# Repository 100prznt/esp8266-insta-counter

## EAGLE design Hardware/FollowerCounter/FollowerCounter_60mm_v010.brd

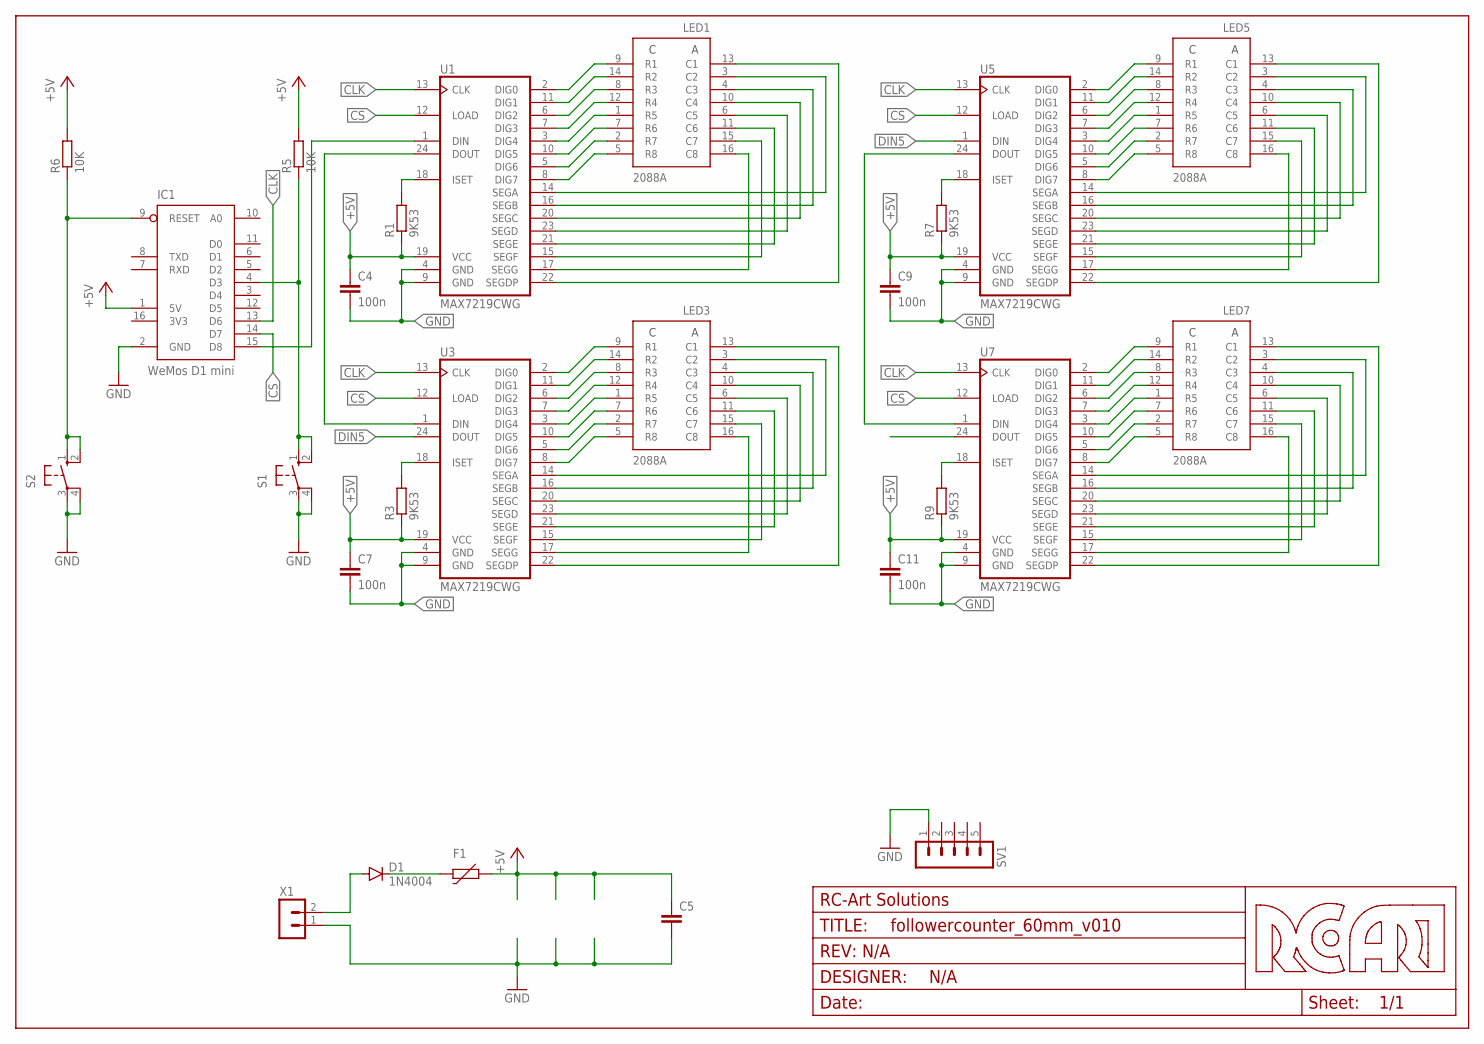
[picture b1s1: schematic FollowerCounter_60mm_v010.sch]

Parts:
C4, C7, C9, C11: 100n; C0805
C5: C-EUC0805; C0805
D1: 1N4004; DO41-10
F1: MF-MSMF075/24-EU; 1812
FRAME1: MF_FRAMEDEFAULT; MF_FRAME_DEFAULT
IC1: WeMos D1 mini; D1_MINI
LED1, LED3, LED5, LED7: 2088A; 8X8_60X60
R1, R3, R7, R9: 9K53; R0805
R5, R6: 10K; R0805
S1, S2: 10-XXS; B3FS-10XX
SV1: MA05-1
U1, U3, U5, U7: MAX7219CWG; SO24L
X1: MA02-1

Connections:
+5V: C4.1, C5.1, C7.1, C9.1, C11.1, F1.1, IC1.1 (5V), R1.1, R3.1, R5.2, R6.2, R7.1, R9.1, U1.19 (VCC), U3.19 (VCC), U5.19 (VCC), U7.19 (VCC)
CLK: IC1.13 (D6), U1.13 (CLK), U3.13 (CLK), U5.13 (CLK), U7.13 (CLK)
COL9: LED1.16 (C8), U1.17 (SEGG)
COL10: LED1.15 (C7), U1.15 (SEGF)
COL11: LED1.11 (C6), U1.21 (SEGE)
COL12: LED1.6 (C5), U1.23 (SEGD)
COL13: LED1.10 (C4), U1.20 (SEGC)
COL14: LED1.4 (C3), U1.16 (SEGB)
COL15: LED1.3 (C2), U1.14 (SEGA)
COL16: LED1.13 (C1), U1.22 (SEGDP)
COL25: LED3.16 (C8), U3.17 (SEGG)
COL26: LED3.15 (C7), U3.15 (SEGF)
COL27: LED3.11 (C6), U3.21 (SEGE)
COL28: LED3.6 (C5), U3.23 (SEGD)
COL29: LED3.10 (C4), U3.20 (SEGC)
COL30: LED3.4 (C3), U3.16 (SEGB)
COL31: LED3.3 (C2), U3.14 (SEGA)
COL32: LED3.13 (C1), U3.22 (SEGDP)
COL41: LED5.16 (C8), U5.17 (SEGG)
COL42: LED5.15 (C7), U5.15 (SEGF)
COL43: LED5.11 (C6), U5.21 (SEGE)
COL44: LED5.6 (C5), U5.23 (SEGD)
COL45: LED5.10 (C4), U5.20 (SEGC)
COL46: LED5.4 (C3), U5.16 (SEGB)
COL47: LED5.3 (C2), U5.14 (SEGA)
COL48: LED5.13 (C1), U5.22 (SEGDP)
COL57: LED7.16 (C8), U7.17 (SEGG)
COL58: LED7.15 (C7), U7.15 (SEGF)
COL59: LED7.11 (C6), U7.21 (SEGE)
COL60: LED7.6 (C5), U7.23 (SEGD)
COL61: LED7.10 (C4), U7.20 (SEGC)
COL62: LED7.4 (C3), U7.16 (SEGB)
COL63: LED7.3 (C2), U7.14 (SEGA)
COL64: LED7.13 (C1), U7.22 (SEGDP)
CS: IC1.14 (D7), U1.12 (LOAD), U3.12 (LOAD), U5.12 (LOAD), U7.12 (LOAD)
DIN1: IC1.15 (D8), U1.1 (DIN)
DIN5: U3.24 (DOUT), U5.1 (DIN)
DOUT1: U1.24 (DOUT), U3.1 (DIN)
DOUT5: U5.24 (DOUT), U7.1 (DIN)
DOUT7: U7.24 (DOUT)
GND: C4.2, C5.2, C7.2, C9.2, C11.2, IC1.2 (GND), S1.3, S1.4 (P1), S2.3, S2.4 (P1), SV1.1, U1.4 (GND), U1.9 (GND), U3.4 (GND), U3.9 (GND), U5.4 (GND), U5.9 (GND), U7.4 (GND), U7.9 (GND), X1.1
ISET1: R1.2, U1.18 (ISET)
ISET3: R3.2, U3.18 (ISET)
ISET5: R7.2, U5.18 (ISET)
ISET7: R9.2, U7.18 (ISET)
unnamed: IC1.4 (D3), R5.1, S1.1 (S), S1.2 (S1)
unnamed: IC1.9 (RESET), R6.1, S2.1 (S), S2.2 (S1)
unnamed: D1.A, X1.2
unnamed: D1.C, F1.2
ROW9: LED1.9 (R1), U1.2 (DIG0)
ROW10: LED1.14 (R2), U1.11 (DIG1)
ROW11: LED1.8 (R3), U1.6 (DIG2)
ROW12: LED1.12 (R4), U1.7 (DIG3)
ROW13: LED1.1 (R5), U1.3 (DIG4)
ROW14: LED1.7 (R6), U1.10 (DIG5)
ROW15: LED1.2 (R7), U1.5 (DIG6)
ROW16: LED1.5 (R8), U1.8 (DIG7)
ROW25: LED3.9 (R1), U3.2 (DIG0)
ROW26: LED3.14 (R2), U3.11 (DIG1)
ROW27: LED3.8 (R3), U3.6 (DIG2)
ROW28: LED3.12 (R4), U3.7 (DIG3)
ROW29: LED3.1 (R5), U3.3 (DIG4)
ROW30: LED3.7 (R6), U3.10 (DIG5)
ROW31: LED3.2 (R7), U3.5 (DIG6)
ROW32: LED3.5 (R8), U3.8 (DIG7)
ROW41: LED5.9 (R1), U5.2 (DIG0)
ROW42: LED5.14 (R2), U5.11 (DIG1)
ROW43: LED5.8 (R3), U5.6 (DIG2)
ROW44: LED5.12 (R4), U5.7 (DIG3)
ROW45: LED5.1 (R5), U5.3 (DIG4)
ROW46: LED5.7 (R6), U5.10 (DIG5)
ROW47: LED5.2 (R7), U5.5 (DIG6)
ROW48: LED5.5 (R8), U5.8 (DIG7)
ROW57: LED7.9 (R1), U7.2 (DIG0)
ROW58: LED7.14 (R2), U7.11 (DIG1)
ROW59: LED7.8 (R3), U7.6 (DIG2)
ROW60: LED7.12 (R4), U7.7 (DIG3)
ROW61: LED7.1 (R5), U7.3 (DIG4)
ROW62: LED7.7 (R6), U7.10 (DIG5)
ROW63: LED7.2 (R7), U7.5 (DIG6)
ROW64: LED7.5 (R8), U7.8 (DIG7)

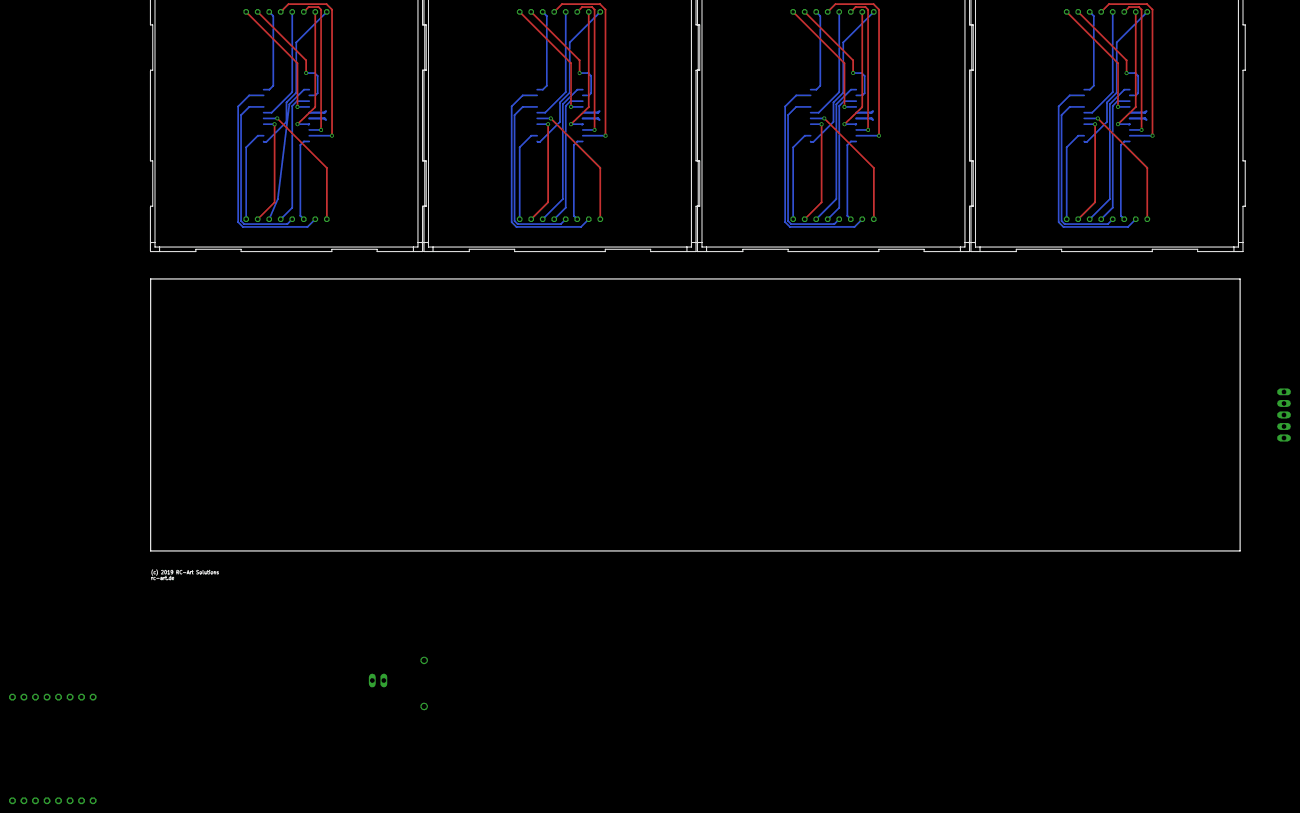
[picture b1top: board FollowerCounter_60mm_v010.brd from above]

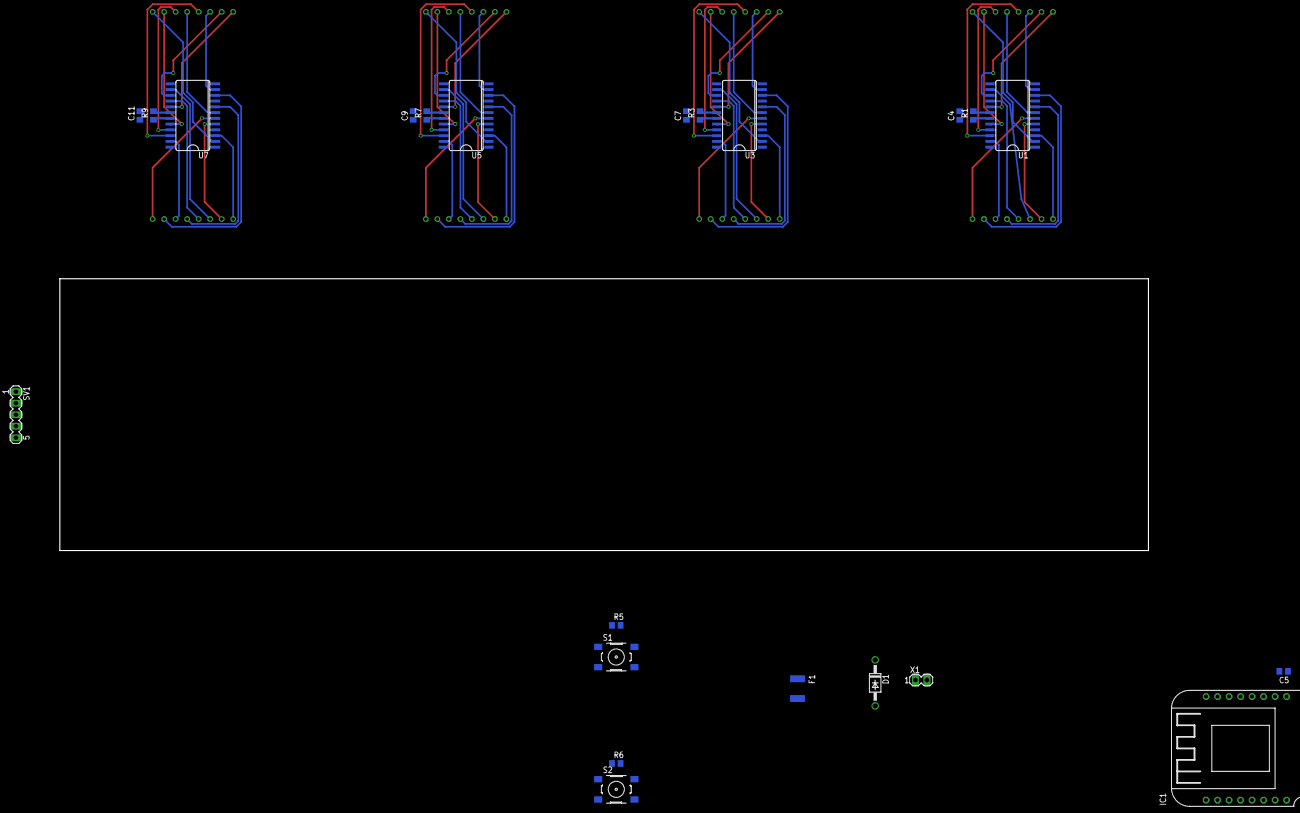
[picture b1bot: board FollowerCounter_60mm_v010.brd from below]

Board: 2 copper layers, 27 parts (22 on the bottom side), 80 nets.

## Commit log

2020-07-29 Initial commit Eagle files :octocat:

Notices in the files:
parts and their libraries:
rca-frames: (c) 2019 RC-Art Solutions
fuse-bourns: Creative Commons Attribution-ShareAlike 3.0 Unported (CC BY-SA 3.0), http://creativecommons.org/licenses/by-sa/3.0/.
